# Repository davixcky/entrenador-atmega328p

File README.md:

# Entrenador ATmega328P

*English: [README.en.md](README.en.md) · Sitio web: <https://davixcky.github.io/entrenador-atmega328p/>*

Proyecto de **Sistemas Embebidos 1 — Actividad 10.1.12**. Entrenador con ATmega328P a 16 MHz, potenciómetro, DIP switch, 8 LEDs y 2 displays de 7 segmentos, que se programa desde una app de escritorio con un diagrama de nodos o con código en español.

**Estado:** hardware armado y funcionando. Firmware, app, biblioteca de Arduino, diseño KiCad y presentación en este repositorio.

## Documentación

| Archivo | Contenido |
|---|---|
| [Guía de conexión y uso](GUIA-USO.md) · [PDF](GUIA-USO.pdf) · [English](USER-GUIDE.md) | Cables Uno ↔ entrenador, preparación, uso diario y solución de problemas |
| [Esquemático](kicad/esquematico.pdf) · [Conexiones](kicad/CONEXIONES.md) | Circuito y cableado pin a pin |
| [App de programación](app/README.md) | Diagrama de nodos y código, monitor en vivo, código generado y grabación |
| [Lenguaje del entrenador](app/lenguaje/README.md) · [English](app/lenguaje/README.en.md) | Sintaxis, funciones, diagrama y traducción a Arduino |
| [Biblioteca Entrenador](firmware/libraries/Entrenador/README.md) | Biblioteca de Arduino del hardware, con los nombres del lenguaje |
| [Registro técnico](REGISTRO-TECNICO.md) | Procedimientos, pruebas y notas del desarrollo |
| [Proyecto KiCad](kicad/entrenador-atmega328p.kicad_pro) · [Fabricación](kicad/fabricacion/) | Diseño de PCB y archivos de fabricación |
| [Presentación PDF](presentacion/presentacion-final.pdf) · [PowerPoint](presentacion/presentacion-final.pptx) · [Guion](presentacion/guion.pdf) | Exposición del proyecto |
| [Sitio web](web/README.md) | Fuente del sitio (Astro), publicado en GitHub Pages |

## Cómo se usa

```text
 PC (app) ──USB──> Arduino Uno ──ISP D10..D13──> ATmega328P del entrenador
                    (puente-uno) ──serie D2/D3───> (firmware bloques)
```

1. Cablear el Uno al entrenador como dice la [guía](GUIA-USO.md#2-conexiones).
2. Abrir la app ([`app/`](app/README.md)), grabar el puente en el Uno y el firmware en el entrenador desde **Firmware**.
3. **Conectar**, escribir el programa en **Diagrama** o **Código** y pulsar **▶ Ejecutar**.

```text
// Cuenta de 00 a 99
cuenta = 0
siempre {
  mostrar(cuenta)
  leds(cuenta)
  esperar(300)
  cuenta += 1
  si cuenta > 99 {
    cuenta = 0
  }
}
```

**Generado** muestra el mismo programa como sketch de Arduino con la biblioteca [`Entrenador`](firmware/libraries/Entrenador/README.md), para compilarlo en el IDE de Arduino.

## Firmware

| Carpeta | Qué hace |
|---|---|
| [`firmware/bloques`](firmware/bloques/bloques.ino) | Firmware de la app: recibe programas por serie y los corre en una máquina virtual |
| [`firmware/puente-uno`](firmware/puente-uno/puente-uno.ino) | Para el Uno: ArduinoISP más puente serie hacia el entrenador |
| [`firmware/libraries/Entrenador`](firmware/libraries/Entrenador/README.md) | Hardware compartido: multiplexado con Timer2, cableado del bus, entradas |
| [`firmware/entrenador`](firmware/entrenador/entrenador.ino) | Firmware original sin app: cuatro modos elegidos con el DIP |
| `firmware/prueba-*` | Sketches de prueba del hardware |

El firmware original (`entrenador`) usa SW2/SW1 del DIP para elegir el modo; **1 significa interruptor cerrado**:

| SW2 SW1 | Modo | Función |
|---|---|---|
| 00 | ADC | Potenciómetro en 00–99 y barra de LEDs |
| 01 | Contador | Cuenta 00–99; velocidad ajustable con el potenciómetro |
| 10 | DIP | Muestra 02, 06, 10 o 14 al cambiar SW3/SW4 |
| 11 | Secuencia | LED que recorre ambos sentidos; velocidad ajustable |

Para compilarlo y cargarlo con el Uno como ISP:

```bash
arduino-cli compile -b arduino:avr:uno firmware/entrenador
arduino-cli upload -b arduino:avr:uno -P arduinoasisp \
  -p <puerto-del-uno> firmware/entrenador
```

`PCB 2` (por defecto) es el cableado de la placa armada; `PCB 1`, el de la PCB de KiCad, y `PCB 0`, el de protoboard. Más detalles en el [registro técnico](REGISTRO-TECNICO.md#7-programación-arduino-uno-como-isp).

Las fotos del desarrollo están en [`capturas/`](capturas/). Para editar o presentar las diapositivas, consultar [`presentacion/`](presentacion/README.md).

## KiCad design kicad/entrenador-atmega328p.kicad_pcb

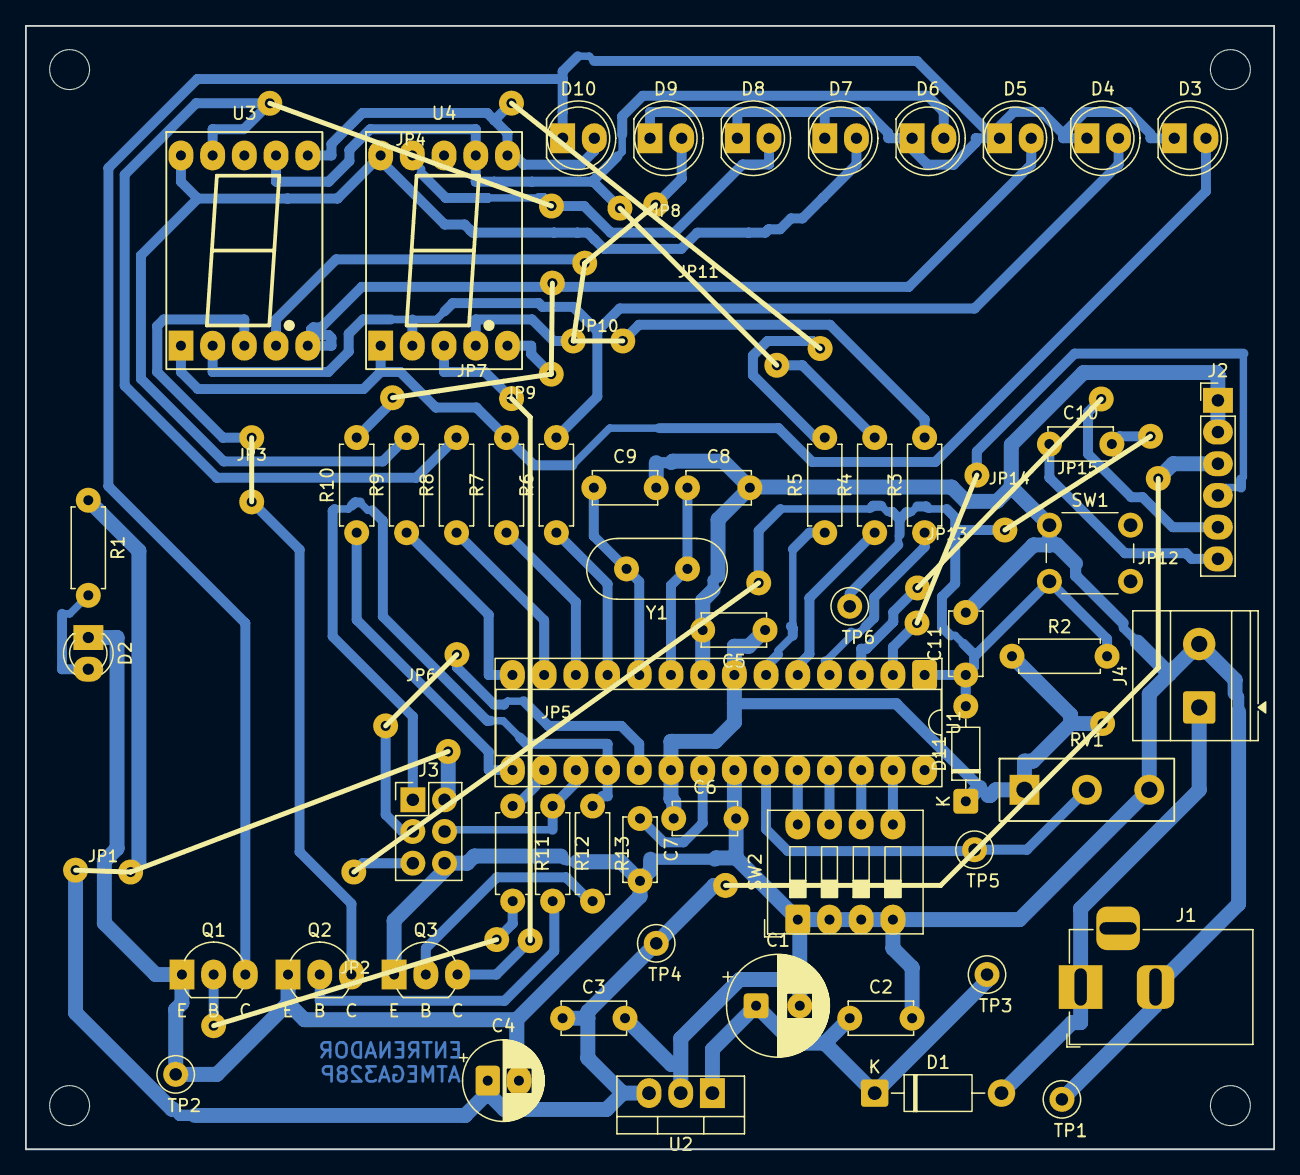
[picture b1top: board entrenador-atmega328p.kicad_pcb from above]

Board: 2 copper layers, 100.0 x 90.0 mm, 75 parts (0 on the bottom side), 43 nets.

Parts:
C1: 100uF/25V; CP_Radial_D8.0mm_P3.50mm
C2: 0.33uF; C_Disc_D5.0mm_W2.5mm_P5.00mm
C3, C5, C6, C7, C10: 0.1uF; C_Disc_D5.0mm_W2.5mm_P5.00mm
C4: 100uF/16V; CP_Radial_D6.3mm_P2.50mm
C8, C9: 22pF; C_Disc_D5.0mm_W2.5mm_P5.00mm
C11: 10nF; C_Disc_D5.0mm_W2.5mm_P5.00mm
D1: 1N4007; D_DO-41_SOD81_P10.16mm_Horizontal
D2: LED ON; LED_D3.0mm
D3: LED0; LED_D5.0mm
D4: LED1; LED_D5.0mm
D5: LED2; LED_D5.0mm
D6: LED3; LED_D5.0mm
D7: LED4; LED_D5.0mm
D8: LED5; LED_D5.0mm
D9: LED6; LED_D5.0mm
D10: LED7; LED_D5.0mm
D11: 1N4148; D_DO-35_SOD27_P7.62mm_Horizontal
H1, H2, H3, H4: MountingHole_3.2mm_M3
J1: 9-12 V DC; BarrelJack_Horizontal
J2: FTDI; PinHeader_1x06_P2.54mm_Vertical
J3: ICSP; PinHeader_2x03_P2.54mm_Vertical
J4: Bornera 9-12 V; TerminalBlock_Phoenix_MKDS-1,5-2-5.08_1x02_P5.08mm_Horizont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
JP1, JP2, JP3, JP4, JP5, JP6, JP7, JP8, JP9, JP10, JP11, JP12, JP13, JP14, JP15: puente; Puente_alambre
Q1, Q2, Q3: 2N2222; TO-92_Inline_Wide
R1, R11, R12, R13: 1k; R_Axial_DIN0207_L6.3mm_D2.5mm_P7.62mm_Horizontal
R2: 10k; R_Axial_DIN0207_L6.3mm_D2.5mm_P7.62mm_Horizontal
R3, R4, R5, R6, R7, R8, R9, R10: 220; R_Axial_DIN0207_L6.3mm_D2.5mm_P7.62mm_Horizontal
RV1: 10k; Pot_3pin_P5.00mm
SW1: Pulsador; SW_PUSH_6mm
SW2: DIP x4; SW_DIP_SPSTx04_Slide_9.78x12.34mm_W7.62mm_P2.54mm
TP1, TP2: GND; TestPoint_Loop_D2.50mm_Drill1.0mm
TP3: VIN; TestPoint_Loop_D2.50mm_Drill1.0mm
TP4: +5V; TestPoint_Loop_D2.50mm_Drill1.0mm
TP5: POT; TestPoint_Loop_D2.50mm_Drill1.0mm
TP6: RESET; TestPoint_Loop_D2.50mm_Drill1.0mm
U1: ATmega328P-PU; DIP-28_W7.62mm_Socket
U2: LM7805; TO-220-3_Vertical
U3: 5161AS DECENAS; Display_5161AS
U4: 5161AS UNIDADES; Display_5161AS
Y1: 16MHz; Crystal_HC49-4H_Vertical

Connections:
+5V: C3.1, C4.1, C5.1, C6.1, D11.1, J2.3, J3.2, JP1.1, JP12.1, R1.1, R2.1, RV1.1, TP4.1, U1.7, U1.20, U2.3
/AREF: C7.1, U1.21
/BUS0: R3.1, U1.4
/BUS1: R4.1, U1.5
/BUS2: R5.1, U1.6
/BUS3: R6.1, U1.11
/BUS4: R7.1, U1.12
/BUS5: R8.1, U1.13
/BUS6: R9.1, U1.14
/BUS7: R10.1, U1.15
/DIP1: SW2.8, U1.24
/DIP2: SW2.7, U1.25
/DIP3: SW2.6, U1.26
/DIP4: SW2.5, U1.27
/DTR: C10.1, J2.6
/K_DEC: JP3.1, Q2.3, U3.3, U3.8
/K_LEDS: D3.1, D4.1, D5.1, D6.1, D7.1, D8.1, D9.1, D10.1, Q1.3
/K_UNI: JP9.1, Q3.3, U4.3, U4.8
/POT: RV1.2, TP5.1, U1.23
/RESET: C10.2, C11.1, D11.2, J3.5, JP5.1, JP15.1, R2.2, SW1.2, TP6.1, U1.1
/RXD: J2.4, JP13.1, U1.2
/SCK: J3.3, JP6.1, U1.19
/SEG_A: D9.2, JP10.1, R3.2, U3.4, U4.4
/SEG_B: D6.2, JP11.1, R4.2, U3.7, U4.7
/SEG_C: D10.2, JP8.1, R5.2, U3.6, U4.6
/SEG_D: D4.2, R6.2, U3.2, U4.2
/SEG_DP: D5.2, JP7.1, R10.2, U3.5, U4.5
/SEG_E: D3.2, R7.2, U3.1, U4.1
/SEG_F: D8.2, JP4.1, R8.2, U3.9, U4.9
/SEG_G: D7.2, R9.2, U3.10, U4.10
/SEL_DEC: J3.4, R12.1, U1.17
/SEL_LED: R11.1, U1.16
/SEL_UNI: J3.1, R13.1, U1.18
/TXD: J2.5, JP14.1, U1.3
/VIN: C1.1, C2.1, D1.1, TP3.1, U2.1
/VIN_RAW: D1.2, J1.1, J4.1
/XTAL1: C8.1, U1.9, Y1.1
/XTAL2: C9.1, U1.10, Y1.2
GND: C1.2, C2.2, C3.2, C4.2, C5.2, C6.2, C7.2, C8.2, C9.2, C11.2, D2.1, J1.2, J2.1, J2.2, J3.6, J4.2, Q1.1, Q2.1, Q3.1, RV1.3, SW1.1, SW2.1, SW2.2, SW2.3, SW2.4, TP1.1, TP2.1, U1.8, U1.22, U2.2
unnamed: D2.2, R1.2
unnamed: JP2.1, Q1.2, R11.2
unnamed: Q2.2, R12.2
unnamed: Q3.2, R13.2

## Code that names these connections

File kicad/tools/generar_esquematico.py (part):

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    d1 = sh.part('Diode:1N4007', 'D1', '1N4007', 50.8, yr, r=180,
                 footprint='Diode_THT:D_DO-41_SOD81_P10.16mm_Horizontal')
    sh.cable(j1['1'], (33.02, yr), (38.1, yr), d1['2'])
    sh.label('VIN_RAW', 33.02, yr, 'R')
    sh.net('VIN_RAW', ('J1', '1'), ('D1', '2'))
    xg = j1['2'][0] + 5.08
    yf = j1['2'][1] + 5.08
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    sh.box(157.48, 15.24, 213.36, 96.52, 'RELOJ 16 MHz')
    yx = 40.64
    y1 = sh.part('Device:Crystal', 'Y1', '16MHz', 185.42, yx, footprint='Crystal:Crystal_HC49-4H_Vertical')
    for ref, xc, pin, name, xe, d in (('C8', 175.26, '1', 'XTAL1', 165.1, 'L'),
                                      ('C9', 195.58, '2', 'XTAL2', 205.74, 'R')):
        c = sh.part('Device:C', ref, '22pF', xc, yx + 12.7, footprint=FP_C)
        sh.cable(y1[pin], (xc, yx), (xe, yx))
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    yd = j2['6'][1]
    c10 = sh.part('Device:C', 'C10', '0.1uF', 330.2, yd, r=90, footprint=FP_C, fields=HORIZ)
    sh.cable(j2['6'], (316.23, yd), c10['1'])
    sh.label('DTR', 316.23, yd, 'R')
    sh.cable(c10['2'], (345.44, yd))
    sh.label('RESET', 345.44, yd, 'R')
    sh.net('DTR', ('J2', '6'), ('C10', '1'))
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    for i in range(7):
        sh.wire(kx[i][0], yb, kx[i + 1][0], yb)
    sh.wire(kx[-1][0], yb, kx[-1][0] + 7.62, yb)
    sh.label('K_LEDS', kx[-1][0] + 7.62, yb, 'R')
    sh.text('SEG_A..SEG_DP = líneas del bus que salen de R3..R10 (bit 0..7).\n'
            'Cableado de la placa armada (medido con firmware/prueba-mapeo):\n'
            'LEDi = bit i (LED0 abajo). Segmentos a=6 b=4 c=0 d=7 e=2 f=5 g=3 dp=1.\n'
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    sh.power('GND', col[-1][0] - 5.08, col[-1][1], 'L')
    for p in '1234':
        sh.nets[('SW2', p)] = 'GND'
    sh.text('Pull-up interna (INPUT_PULLUP):\ninterruptor cerrado = 0, abierto = 1.\nDIP1..DIP4 → PC1..PC4 (A1..A4)',
            172.72, 256.54)

    # Botones en escalera: una sola entrada analogica (PC5) para B1..B5. R14..R18 en serie
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            '5. PCB de una cara: el DIP lleva las señales en los pines 8–5 y GND en 1–4 para no cruzar\n'
            '    pistas. Puentes de alambre en kicad/fabricacion/PUENTES.md.\n'
            '6. La placa armada se cableó a mano; el orden del bus es el de SALIDAS, no el de la PCB de kicad/.\n'
            '7. Revisar al armar: emisor de Q1 a GND; SEL_LED, SEL_DEC y SEL_UNI a los pines 16, 17 y 18;\n'
            '    GND del Uno unido al de la placa (sin él el ISP lee la firma 00 00 00).',
            17.78, 252.73, size=1.4)

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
